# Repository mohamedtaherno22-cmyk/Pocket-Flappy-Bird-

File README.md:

# Mini Gaming Console For Chrome Dino Game 🦖 # 

A small DIY handheld console inspired by the classic Google Chrome Dinosaur game!. I thought it would be fun to make a dedicated console for the game and i also plan to add other games in the future.

## ✨ Features

Here's what I'm planning to include:

- **ESP32:** The main controller that handles the game and processes inputs.
- **Display:** Shows the dinosaur, obstacles, and the rest of the game.
- **Joystick:** Used to control the dinosaur and navigate the game.
- **Physical buttons:** For additional controls and interactions.
- **Vibration motor:** Adds a little haptic feedback while playing.
- **Custom PCBs:** Two separate boards to keep the components organized.
- **3D component layout:** A preview of how everything fits together inside the console.

## 3d image

## PCB

I originally tried to fit everything onto one board, but I wasn't really happy with how it looked. So, I decided to split the design into two boards instead.

- **Controller Board:** Holds the joystick, buttons, display connections, and other components.
- **ESP32 Board:** Contains the ESP32 and its supporting circuitry.

The two boards are connected using a bundle of wires and a dedicated connector.

I also wanted to keep the routing as clean as possible, so I managed to route everything using just one copper layer. This should also help reduce manufacturing costs.

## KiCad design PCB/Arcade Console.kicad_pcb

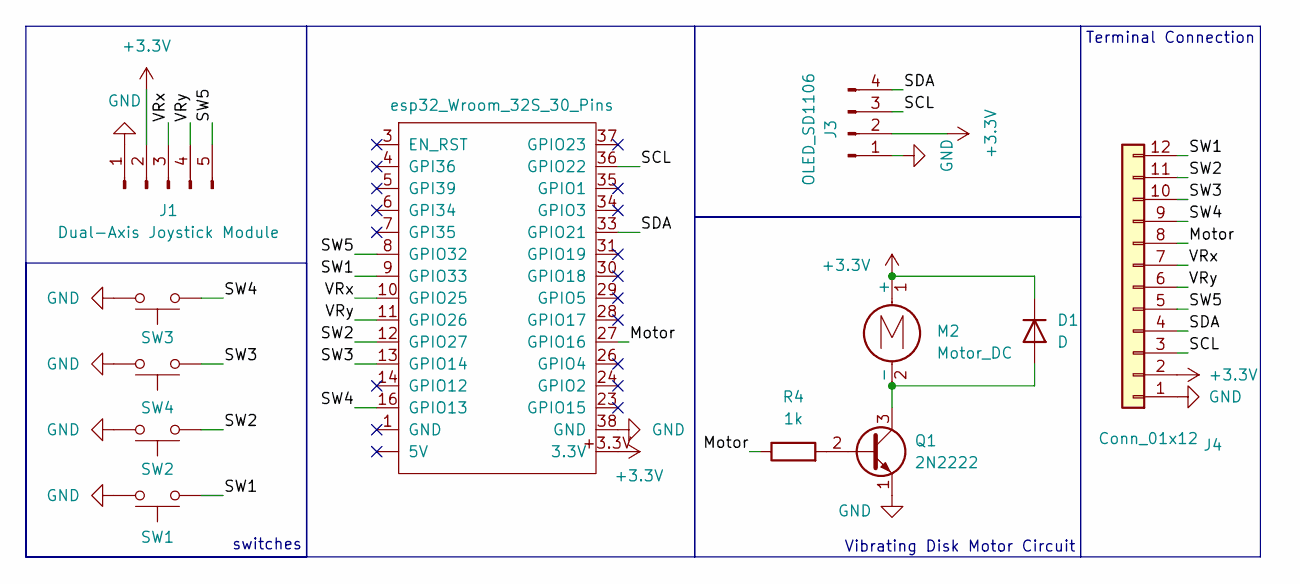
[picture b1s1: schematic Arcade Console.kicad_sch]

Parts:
D1: D; D_DO-35_SOD27_P7.62mm_Horizontal
J1: Dual-Axis Joystick Module; PinHeader_1x05_P2.54mm_Vertical
J3: OLED_SD1106; Display_128x64_096_I2C
J4: Conn_01x12; PinHeader_1x12_P2.00mm_Vertical
M2: Motor_DC; PinHeader_1x02_P2.54mm_Vertical
Q1: 2N2222; TO-92_Inline_Wide
R4: 1k; R_Axial_DIN0204_L3.6mm_D1.6mm_P7.62mm_Horizontal
SW1, SW2, SW3, SW4: SW_Push; SW_PUSH_6mm
U2: esp32_Wroom_32S_30_Pins; THE NEW FOOTPRINTER

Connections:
+3.3V: D1.1 (K), J1.2, J3.2, J4.2, M2.1 (+), U2.+3.3V (3.3V); also elsewhere on the board
/Motor: J4.8, R4.1, U2.27 (GPIO16); also elsewhere on the board
/SCL: J3.3, J4.3, U2.36 (GPIO22); also elsewhere on the board
/SDA: J3.4, J4.4, U2.33 (GPIO21); also elsewhere on the board
/SW1: J4.12, SW1.1, U2.9 (GPIO33); also elsewhere on the board
/SW2: J4.11, SW2.1, U2.12 (GPIO27); also elsewhere on the board
/SW3: J4.10, SW4.1, U2.13 (GPIO14); also elsewhere on the board
/SW4: J4.9, SW3.1, U2.16 (GPIO13); also elsewhere on the board
/SW5: J1.5, J4.5, U2.8 (GPIO32); also elsewhere on the board
/VRx: J1.3, J4.7, U2.10 (GPIO25); also elsewhere on the board
/VRy: J1.4, J4.6, U2.11 (GPIO26); also elsewhere on the board
GND: J1.1, J3.1, J4.1, Q1.1 (E), SW1.2, SW2.2, SW3.2, SW4.2, U2.38 (GND); also elsewhere on the board
unnamed: D1.2 (A), M2.2 (-), Q1.3 (C)
unnamed: Q1.2 (B), R4.2

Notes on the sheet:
Vibrating Disk Motor Circuit
switches
Terminal Connection

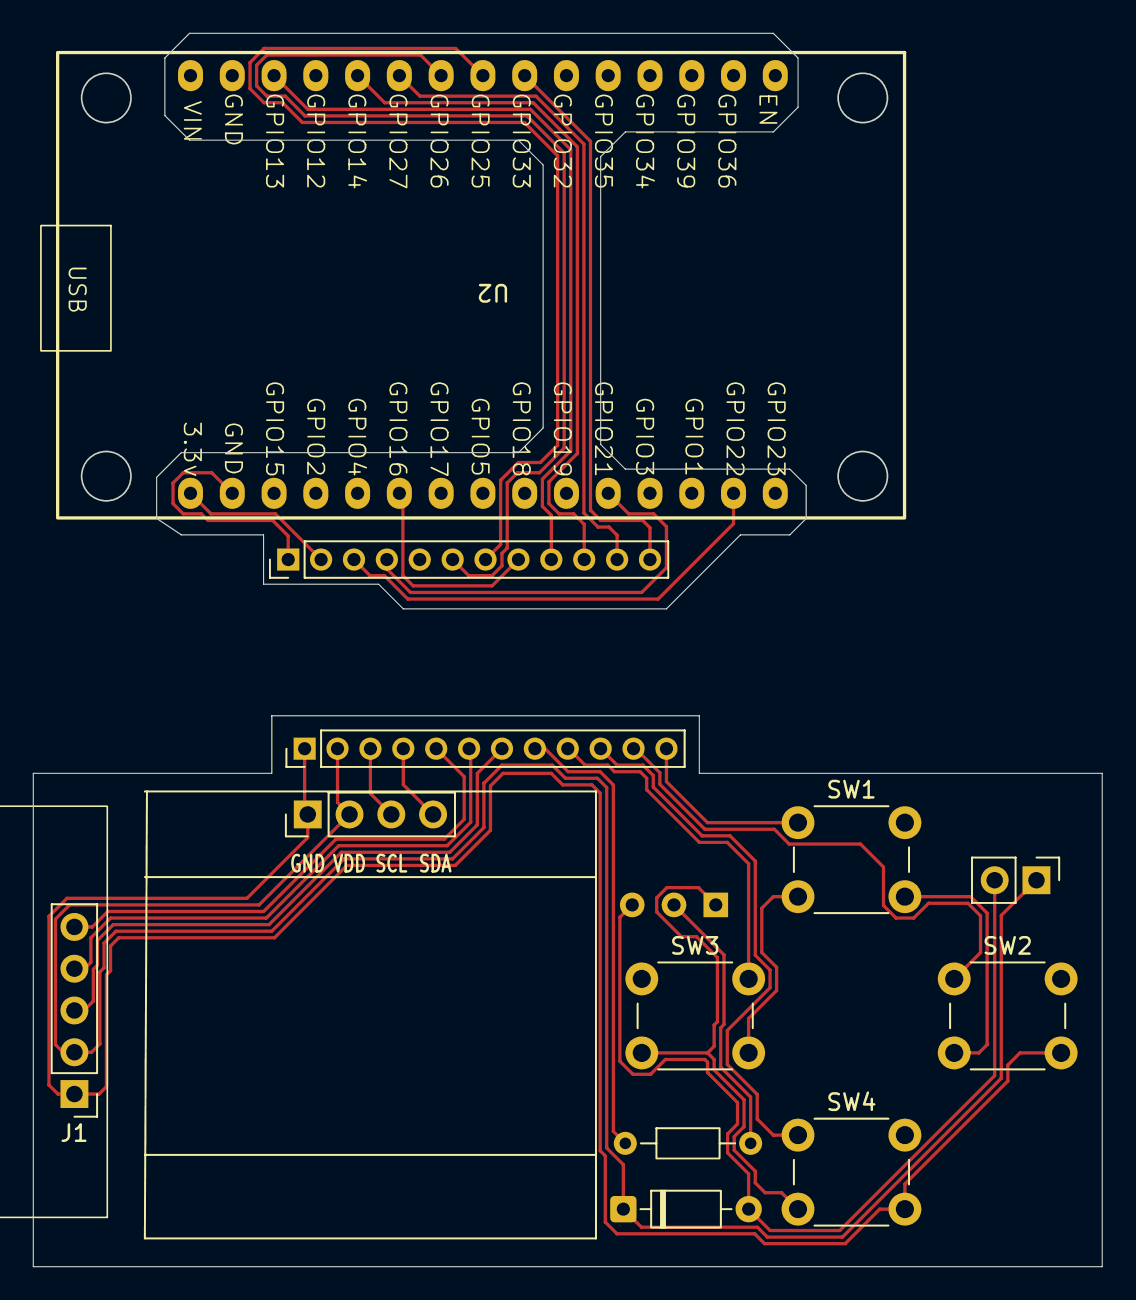
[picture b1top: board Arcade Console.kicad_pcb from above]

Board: 2 copper layers, 65.0 x 33.5 mm, 13 parts (1 on the bottom side), 14 nets.

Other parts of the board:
J4#2: Conn_01x12; PinHeader_1x12_P2.00mm_Vertical

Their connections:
+3.3V: J4#2.2; also elsewhere on the board
/Motor: J4#2.8; also elsewhere on the board
/SCL: J4#2.3; also elsewhere on the board
/SDA: J4#2.4; also elsewhere on the board
/SW1: J4#2.12; also elsewhere on the board
/SW2: J4#2.11; also elsewhere on the board
/SW3: J4#2.10; also elsewhere on the board
/SW4: J4#2.9; also elsewhere on the board
/SW5: J4#2.5; also elsewhere on the board
/VRx: J4#2.7; also elsewhere on the board
/VRy: J4#2.6; also elsewhere on the board
GND: J4#2.1; also elsewhere on the board
